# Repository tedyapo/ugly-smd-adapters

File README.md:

# ugly-smd-adapters
Eagle PCB designs for adapting SMD parts to ugly (or Manhattan) style breadboarding

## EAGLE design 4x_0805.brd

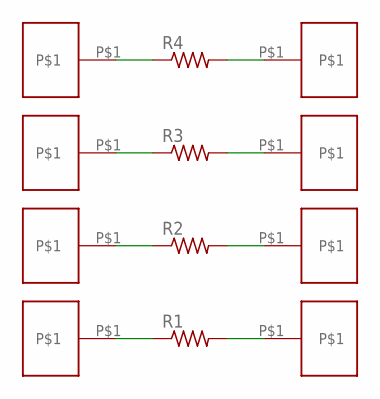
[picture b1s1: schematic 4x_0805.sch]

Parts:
R1, R2, R3, R4: R-US_R0805; R0805
U$1, U$2, U$3, U$4, U$5, U$6, U$7, U$8: PAD100MIL; 100MIL_PAD

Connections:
unnamed: R4.1, U$1.P$1
unnamed: R4.2, U$5.P$1
unnamed: R3.2, U$6.P$1
unnamed: R3.1, U$2.P$1
unnamed: R2.1, U$3.P$1
unnamed: R2.2, U$7.P$1
unnamed: R1.2, U$8.P$1
unnamed: R1.1, U$4.P$1

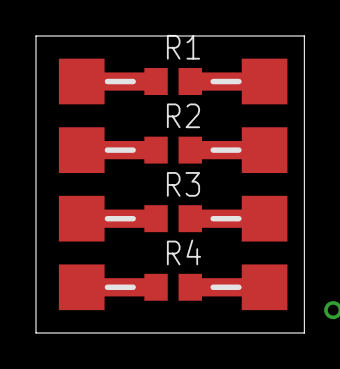
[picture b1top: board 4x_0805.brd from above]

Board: 2 copper layers, 14.9 x 16.5 mm, 12 parts (0 on the bottom side), 8 nets.

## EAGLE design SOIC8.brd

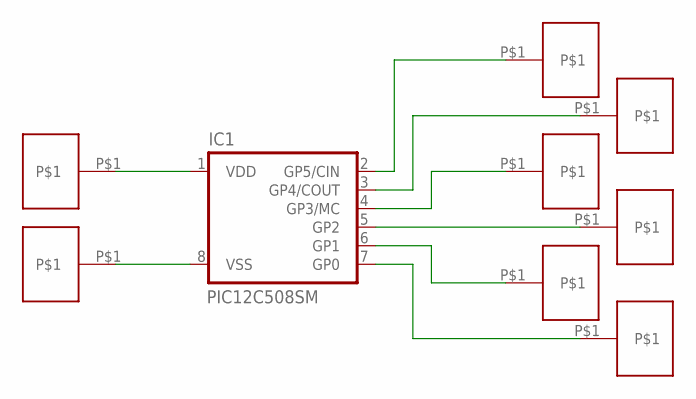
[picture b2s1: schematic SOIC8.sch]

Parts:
IC1: PIC12C508SM; SO-08M
U$1, U$2, U$3, U$4, U$5, U$6, U$7, U$8: PAD50X100MIL; 100X50MIL_PAD

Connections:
unnamed: IC1.1 (VDD), U$1.P$1
unnamed: IC1.8 (VSS), U$2.P$1
unnamed: IC1.2 (GP5/CIN), U$8.P$1
unnamed: IC1.3 (GP4/COUT), U$6.P$1
unnamed: IC1.4 (GP3/MC), U$3.P$1
unnamed: IC1.5 (GP2), U$5.P$1
unnamed: IC1.6 (GP1), U$4.P$1
unnamed: IC1.7 (GP0), U$7.P$1

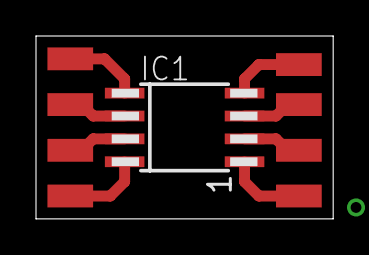
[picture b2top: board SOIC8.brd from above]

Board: 2 copper layers, 16.5 x 10.2 mm, 9 parts (0 on the bottom side), 8 nets.

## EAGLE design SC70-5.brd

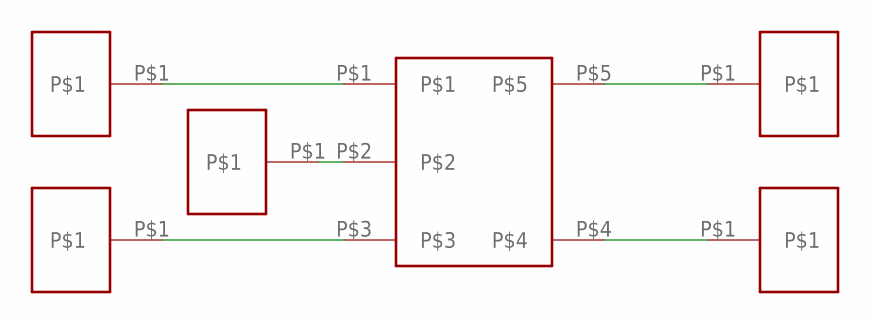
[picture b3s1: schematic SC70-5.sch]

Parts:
U$1: SC70-5SC70-5; SC70-5
U$2, U$3, U$4, U$5, U$6: PAD100MIL; 100MIL_PAD

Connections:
unnamed: U$1.P$1, U$2.P$1
unnamed: U$1.P$2, U$3.P$1
unnamed: U$1.P$3, U$4.P$1
unnamed: U$1.P$5, U$6.P$1
unnamed: U$1.P$4, U$5.P$1

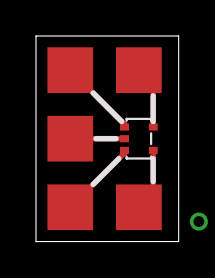
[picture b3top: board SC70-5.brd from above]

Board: 2 copper layers, 7.9 x 11.4 mm, 6 parts (0 on the bottom side), 5 nets.

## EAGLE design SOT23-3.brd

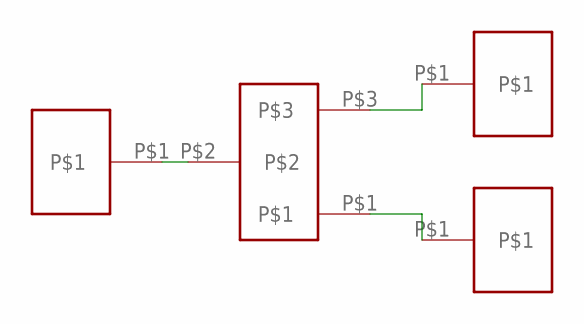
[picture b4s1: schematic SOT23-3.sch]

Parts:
U$1: SOT23-3
U$2, U$3, U$4: PAD; 100MIL_PAD

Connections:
unnamed: U$1.P$2, U$2.P$1
unnamed: U$1.P$3, U$3.P$1
unnamed: U$1.P$1, U$4.P$1

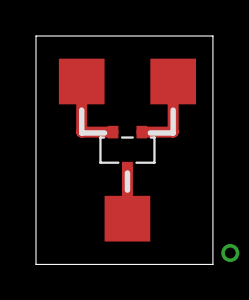
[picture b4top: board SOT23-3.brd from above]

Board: 2 copper layers, 9.8 x 12.7 mm, 4 parts (0 on the bottom side), 3 nets.

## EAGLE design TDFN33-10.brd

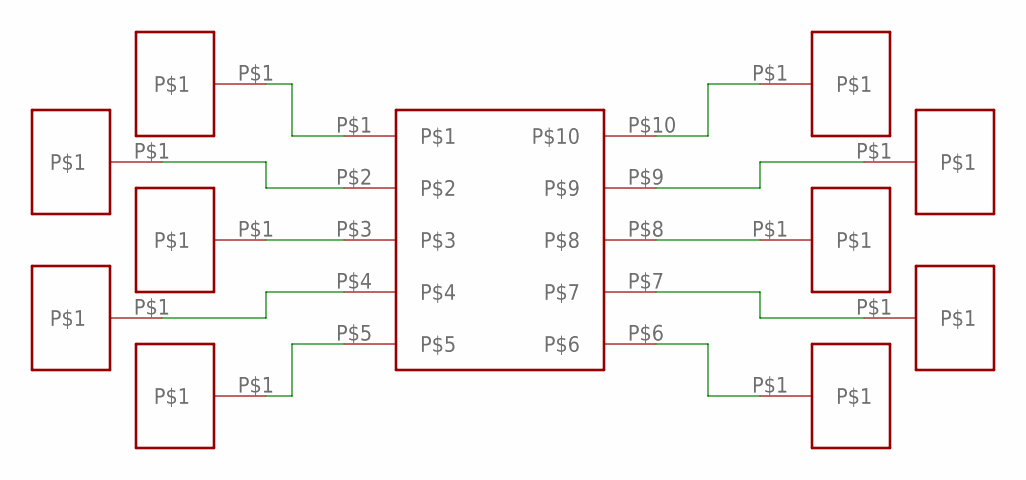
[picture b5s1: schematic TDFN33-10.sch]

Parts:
U$1: TDFN33-10TDFN33-10; TDFN33-10
U$2, U$3, U$4, U$5, U$6, U$7, U$8, U$9, U$10, U$11: PAD50X100MIL; 100X50MIL_PAD

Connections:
unnamed: U$1.P$3, U$2.P$1
unnamed: U$1.P$2, U$3.P$1
unnamed: U$1.P$4, U$4.P$1
unnamed: U$1.P$5, U$6.P$1
unnamed: U$1.P$1, U$5.P$1
unnamed: U$1.P$8, U$7.P$1
unnamed: U$1.P$9, U$8.P$1
unnamed: U$1.P$7, U$9.P$1
unnamed: U$1.P$10, U$10.P$1
unnamed: U$1.P$6, U$11.P$1

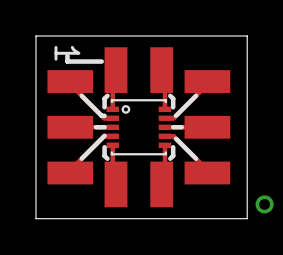
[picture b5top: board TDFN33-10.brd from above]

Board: 2 copper layers, 11.7 x 10.2 mm, 11 parts (0 on the bottom side), 10 nets.

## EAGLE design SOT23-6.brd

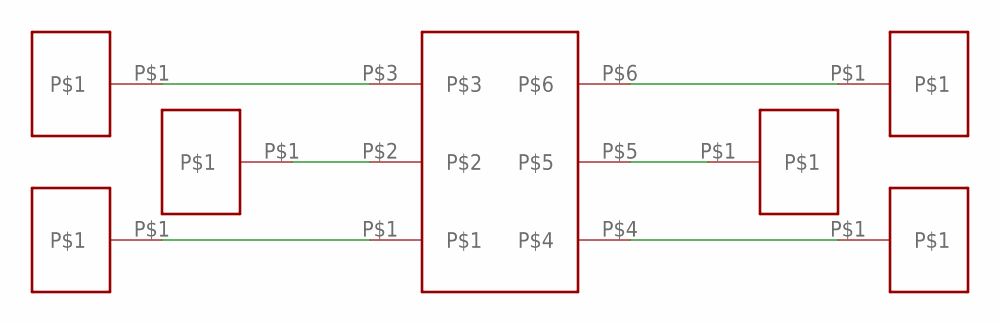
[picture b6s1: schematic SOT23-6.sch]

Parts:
U$1: SOT23-6
U$2, U$3, U$4, U$5, U$6, U$7: PAD50X100MIL; 100X50MIL_PAD

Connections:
unnamed: U$1.P$3, U$3.P$1
unnamed: U$1.P$2, U$2.P$1
unnamed: U$1.P$1, U$4.P$1
unnamed: U$1.P$6, U$6.P$1
unnamed: U$1.P$5, U$5.P$1
unnamed: U$1.P$4, U$7.P$1

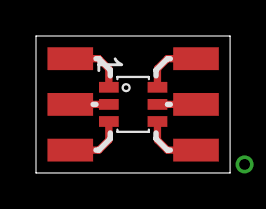
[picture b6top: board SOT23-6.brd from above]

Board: 2 copper layers, 10.8 x 7.6 mm, 7 parts (0 on the bottom side), 6 nets.

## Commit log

2016-07-22 first versions of first set of adapters
2016-07-22 fixed license file
